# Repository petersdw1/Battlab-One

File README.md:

# BattLab-One
A New Tool for Estimating and Optimizing Battery Life for Your Next Internet of Things Project

  - Battlab-One Quick Start Guide

  - BattLab_One_Production_Rev_A.py - Python Application Code for Production version 1.01

  - Production_Rev_A.sch - Schematic in Eagle

  - Production_Rev_A..brd - PCB Layout in Eagle

  - MSP430Firmware.c - Firmware code for the MSP430 for Production Version 1.01

  - BOM_Production_Rev_A - Bill of Materials for Battlab-One Production Rev A

  - 98-bluebird-labs.rules - Linux udev rules for Battlab-One

  See more at www.bluebird-labs.com

# Development

This project uses pipenv to take care of setting up a virtual environment as well as managing the dependencies needed.

1. Install pipenv as describe here https://pypi.org/project/pipenv/
2. Start a terminal and change to the root folder of this project.
3. Run pipenv to setup the environment: `pipenv install --dev`
4. Start the pipenv shell: `pipenv shell`
5. Start the application: `python BattLab_One_V1.0.6.py`

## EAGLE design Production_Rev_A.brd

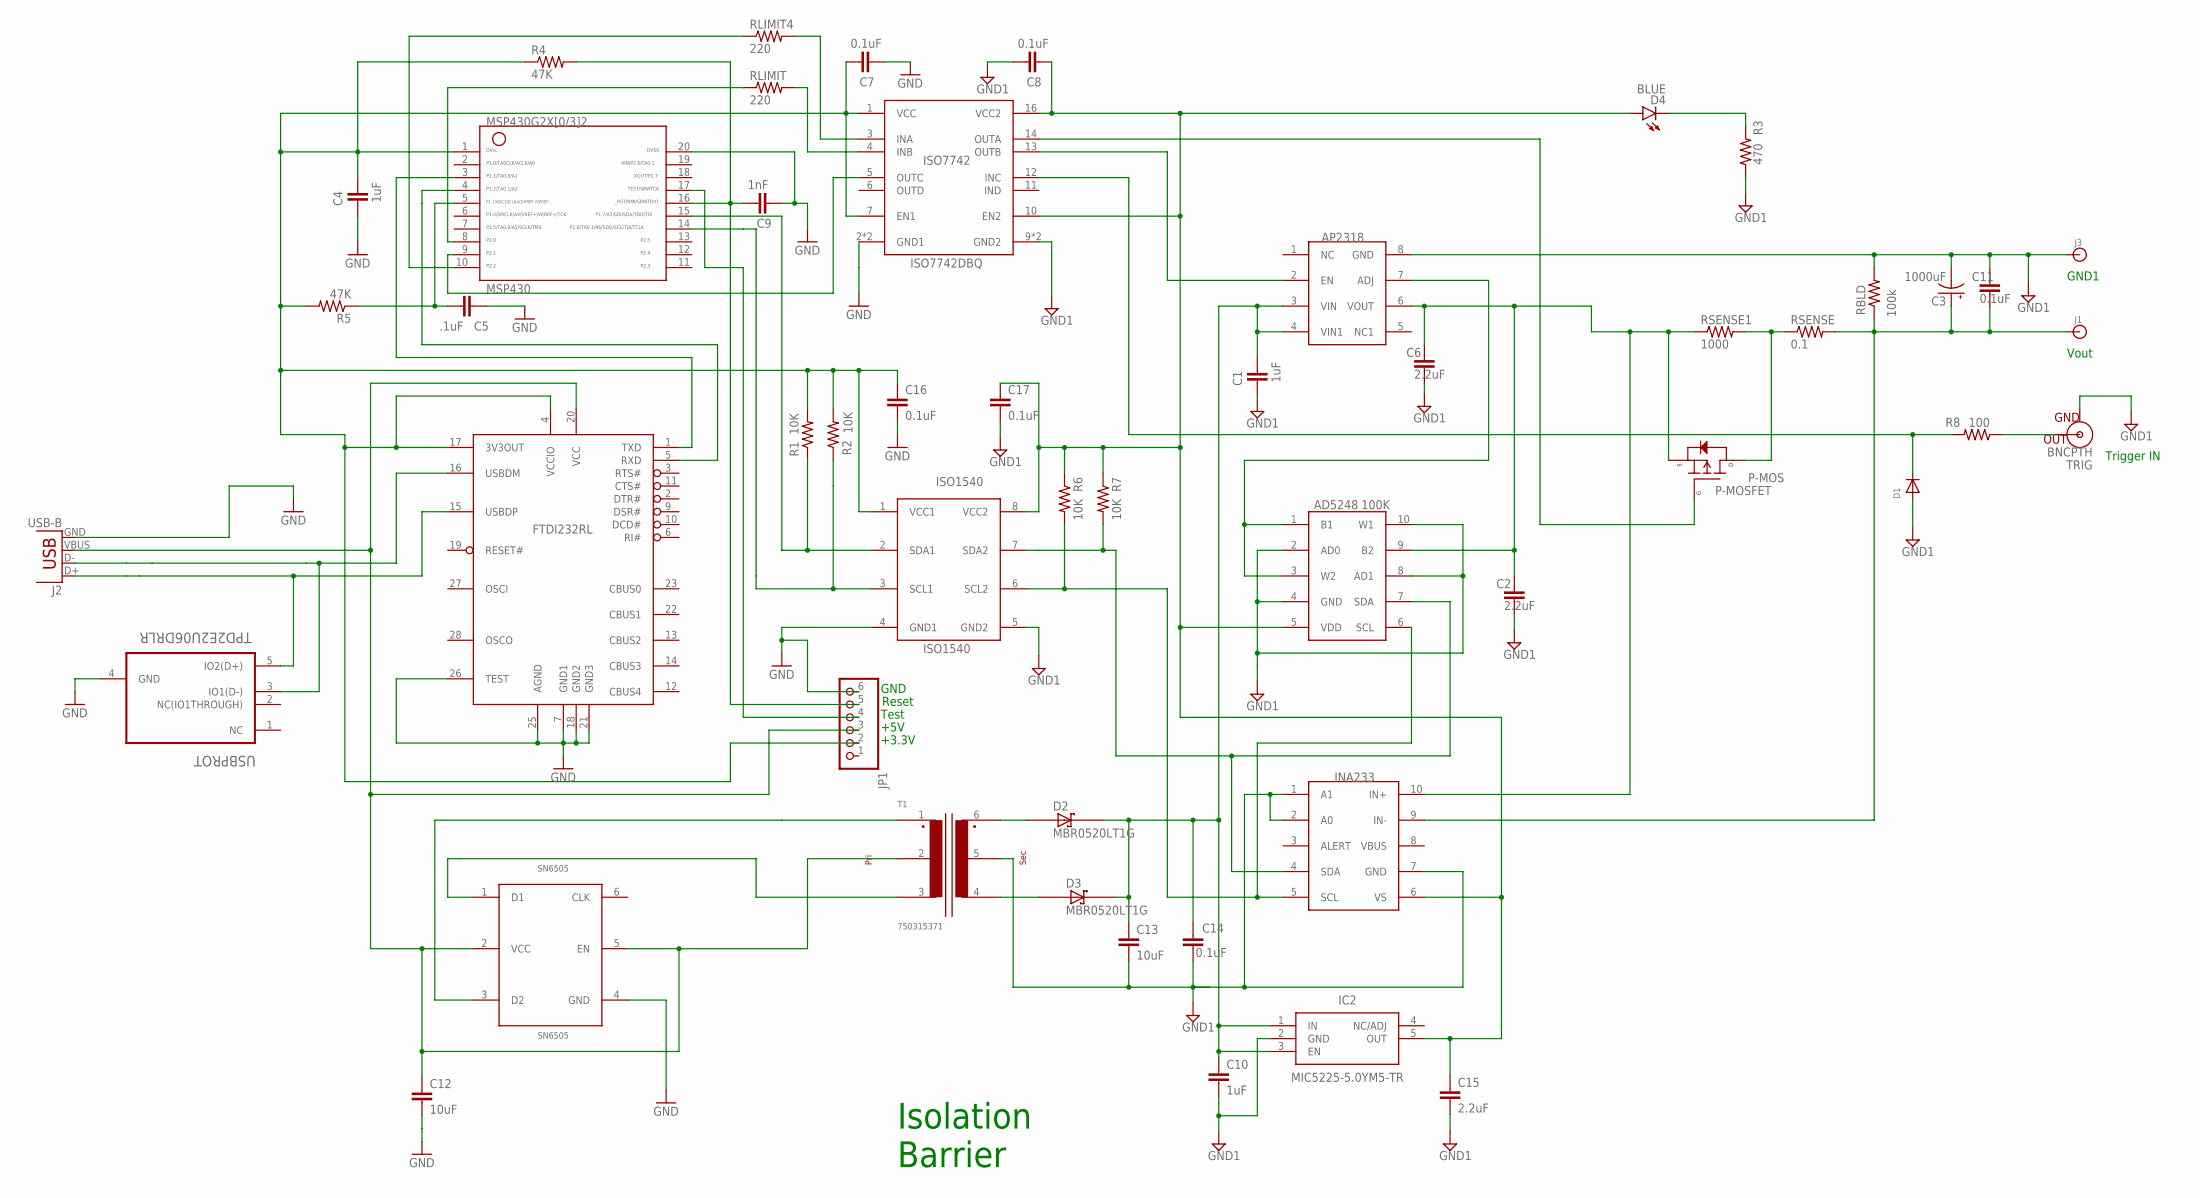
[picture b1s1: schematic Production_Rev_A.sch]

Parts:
AD5248: 100K; MSOP-10
AP2318: AP2318; SOIC-8
C1, C4, C10: 1uF; 1206
C2, C6, C15: 2.2uF; 1206
C3: 1000uF; PANASONIC_F
C5: .1uF; 1206
C7, C8, C11, C14, C16, C17: 0.1uF; 1206
C9: 1nF; 1206
C12, C13: 10uF; 1206
D1: DIODESOD-123; SOD-123
D2, D3: MBR0520LT1G; SOD3716X117(SOD-123)
D4: BLUE; LED-1206
FTDI232RL: FT232RL; SSOP28DB
IC2: MIC5225-5.0YM5-TR; SOT95P280X130-5N
INA233: INA233; VSSOP-10
ISO1540: ISO1540; SOIC127P600X175-8N
ISO7742: ISO7742DBQ; SOP63P599X175-16N
J1, J3: BANANA_CONN
J2: USB-B; USB-B-PTH
JP1: PINHD-1X6; 1X06
MSP430: MSP430; PW20
P-MOS: P-MOSFET; SOT23-3
R1, R2, R6, R7: 10K; 1206
R3: 470; 1206
R4, R5: 47K; 1206
R8: 100; 1206
RBLD: 100k; 1206
RLIMIT, RLIMIT4: 220; 1206
RSENSE: 0.1; 1206
RSENSE1: 1000; 1206
SN6505: SN6505; SOT95P280X145-6N
T1: 750315371; TOR-6P-HT4_SMT_6PIN_(1201)
TRIG: BNCPTH; BNC
USBPROT: TPD2E2U06DRLR; SOT50P160X60-5N

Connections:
3.3V: C4.2, C7.2, C16.1, FTDI232RL.4 (VCCIO), FTDI232RL.17 (3V3OUT), ISO1540.1 (VCC1), ISO7742.1 (VCC), ISO7742.7 (EN1), JP1.2, MSP430.1, R1.2, R2.2, R4.1, R5.2
+5V_LDO: AD5248.5 (VDD), C8.1, C15.1, C17.1, D4.A, IC2.5 (OUT), INA233.6 (VS), ISO1540.8 (VCC2), ISO7742.10 (EN2), ISO7742.16 (VCC2), R6.1, R7.1
GND: C4.1, C5.1, C7.1, C9.1, C12.2, C16.2, FTDI232RL.7 (GND1), FTDI232RL.18 (GND2), FTDI232RL.21 (GND3), FTDI232RL.25 (AGND), FTDI232RL.26 (TEST), ISO1540.4 (GND1), ISO7742.2 (GND1), ISO7742.8 (GND1), J2.GND, JP1.6, MSP430.20, SN6505.4 (GND), USBPROT.4 (GND)
GND1: AD5248.2 (AD0), AD5248.4 (GND), AD5248.8 (AD1), AD5248.10 (W1), AP2318.8 (GND), C1.1, C2.2, C3.-, C6.2, C8.2, C10.2, C11.1, C13.2, C14.2, C15.2, C17.2, D1.A, IC2.2 (GND), INA233.1 (A1), INA233.2 (A0), INA233.7 (GND), ISO1540.5 (GND2), ISO7742.9 (GND2), ISO7742.15 (GND2), J3.P$1, R3.1, RBLD.2, T1.5, TRIG.GND
LDO_EN: ISO7742.4 (INB), RLIMIT.2
LDO_EN1: MSP430.8, RLIMIT.1
LDO_EN2: AP2318.2 (EN), ISO7742.13 (OUTB)
unnamed: P-MOS.3 (D), RSENSE.1, RSENSE1.2
unnamed: AP2318.3 (VIN), AP2318.4 (VIN1), C1.2, C10.1, C13.1, C14.1, D2.1 (C), D3.1 (C), IC2.1 (IN), IC2.3 (EN)
unnamed: D3.2 (A), T1.4
unnamed: D2.2 (A), T1.6
unnamed: AD5248.1 (B1), AD5248.3 (W2), AP2318.7 (ADJ)
unnamed: D4.C, R3.2
unnamed: R8.1, TRIG.S (OUT)
NC: USBPROT.1 (NC)
RESET: C9.2, JP1.5, MSP430.16, R4.2
RS_EN: MSP430.10, RLIMIT4.1
RS_EN1: ISO7742.3 (INA), RLIMIT4.2
RS_EN2: ISO7742.14 (OUTA), P-MOS.1 (G)
SCL1: ISO1540.3 (SCL1), MSP430.14, R2.1
SCL2: AD5248.6 (SCL), INA233.5 (SCL), ISO1540.6 (SCL2), R6.2
SDA1: ISO1540.2 (SDA1), MSP430.15, R1.1
SDA2: AD5248.7 (SDA), INA233.4 (SDA), ISO1540.7 (SDA2), R7.2
TEST: JP1.4, MSP430.17
TRANS1: SN6505.3 (D2), T1.1
TRANS3: SN6505.1 (D1), T1.3
TRIGGER_MSP1: ISO7742.5 (OUTC), MSP430.9
TRIGGER_MSP2: D1.C, ISO7742.12 (INC), R8.2
UART_RX: FTDI232RL.5 (RXD), MSP430.4
UART_TX: FTDI232RL.1 (TXD), MSP430.3
USB+: FTDI232RL.15 (USBDP), J2.D+, USBPROT.5 (IO2(D+))
USB-: FTDI232RL.16 (USBDM), J2.D-, USBPROT.3 (IO1(D-))
VBUS+5V: C12.1, FTDI232RL.20 (VCC), J2.VBUS, JP1.3, SN6505.2 (VCC), SN6505.5 (EN), T1.2
VOUT: C3.+, C11.2, INA233.9 (IN-), J1.P$1, RBLD.1, RSENSE.2
VREF: C5.2, MSP430.5, R5.1
V_OUT: AD5248.9 (B2), AP2318.6 (VOUT), C2.1, C6.1, INA233.10 (IN+), P-MOS.2 (S), RSENSE1.1

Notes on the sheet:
Isolation Barrier
Test
Reset
GND
+5V
GND1
Vout
Trigger IN
+3.3V

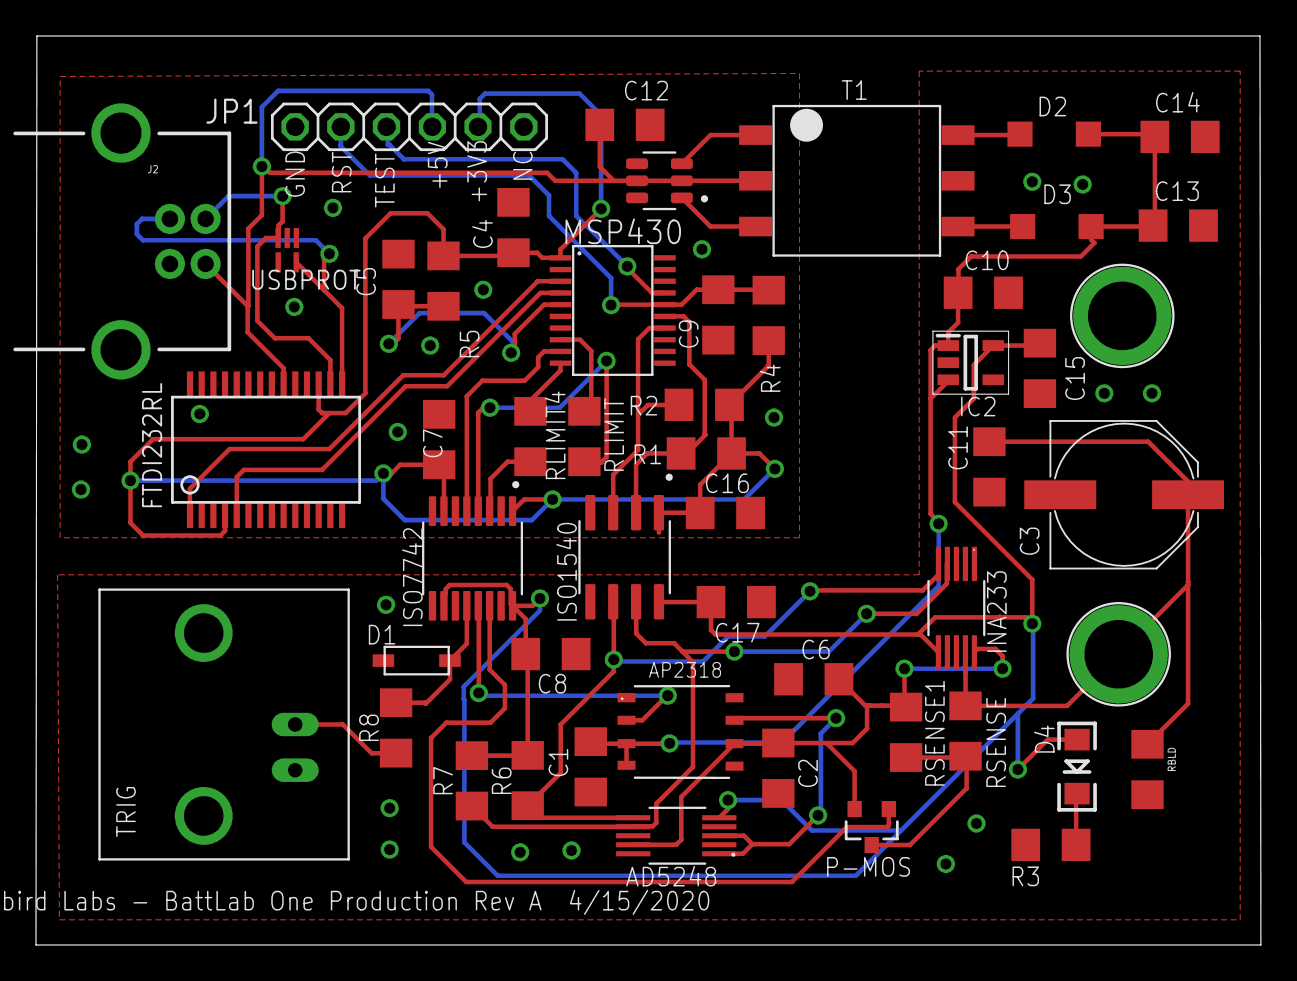
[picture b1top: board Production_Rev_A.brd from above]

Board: 2 copper layers, 68.0 x 50.5 mm, 51 parts (0 on the bottom side), 35 nets.

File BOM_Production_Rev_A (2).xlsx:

Part | Value | Device | Package | Description
AD5248 | 100K | AD5248 | MSOP-10 | Digital potentiometer
AP2318 |  | AP2318 | SOIC-8 | Voltage Regulator
C1 | 1uF | CAP1206 | 1206 | Capacitor
C2 | 2.2uF | CAP1206 | 1206 | Capacitor
C3 | 1000uF | CPOL-USF | PANASONIC_F | POLARIZED CAPACITOR
C4 | 1uF | CAP1206 | 1206 | Capacitor
C5 | .1uF | CAP1206 | 1206 | Capacitor
C6 | 2.2uF | CAP1206 | 1206 | Capacitor
C7 | 0.1uF | CAP1206 | 1206 | Capacitor
C8 | 0.1uF | CAP1206 | 1206 | Capacitor
C9 | 1nF | CAP1206 | 1206 | Capacitor
C10 | 1uF | CAP1206 | 1206 | Capacitor
C11 | 0.1uF | CAP1206 | 1206 | Capacitor
C12 | 10uF | CAP1206 | 1206 | Capacitor
C13 | 10uF | CAP1206 | 1206 | Capacitor
C14 | 0.1uF | CAP1206 | 1206 | Capacitor
C15 | 2.2uF | CAP1206 | 1206 | Capacitor
C16 | 0.1uF | CAP1206 | 1206 | Capacitor
C17 | 0.1uF | CAP1206 | 1206 | Capacitor
D1 |  | DIODESOD-123 | SOD-123 | Diode
D2 | MBR0520LT1G | MBR0520LT1G | SOD3716X117(SOD-123) | Surface Mount Schottky Power Rectifier Plastic SODâˆ’123 Package
D3 | MBR0520LT1G | MBR0520LT1G | SOD3716X117(SOD-123) | Surface Mount Schottky Power Rectifier Plastic SODâˆ’123 Package
D4 | BLUE | LED-BLUE1206 | LED-1206 | Blue LEDs for production use
FTDI232RL |  | FT232RL | SSOP28DB | USB UART
IC2 | MIC5225-5.0YM5-TR | MIC5225-5.0YM5-TR | SOT95P280X130-5N | MICROCHIP - MIC5225-5.0YM5-TR - LDO VOLT REG
INA233 |  | INA233 | VSSOP-10 | Texas Instruments current measurement
ISO1540 | ISO1540 | ISO1540 | SOIC127P600X175-8N | i2c Isolation
ISO7742 | ISO7742DBQ | ISO7742DBQ | SOP63P599X175-16N | High-Efficiency
J1 |  | BANANA_CONN | BANANA_CONN | Through-hole banana jack
J2 | USB-B | USBPTH | USB-B-PTH | USB Connectors
J3 |  | BANANA_CONN | BANANA_CONN | Through-hole banana jack
JP1 |  | PINHD-1X6 | 1X06 | PIN HEADER
MSP430 | MSP430 | G2X[0/3]2---PW20 | PW20 | MSP430G2X[0/3]2
P-MOS | P-MOSFET | P-CHANNEL-MOSFET | SOT23-3 | P-Channel MOSFET Mode Field Effect Transistor
R1 | 10K | RESISTOR1206 | 1206 | Resistor
R2 | 10K | RESISTOR1206 | 1206 | Resistor
R3 | 470 | RESISTOR1206 | 1206 | Resistor
R4 | 47K | RESISTOR1206 | 1206 | Resistor
R5 | 47K | RESISTOR1206 | 1206 | Resistor
R6 | 10K | RESISTOR1206 | 1206 | Resistor
R7 | 10K | RESISTOR1206 | 1206 | Resistor
R8 | 100 | RESISTOR1206 | 1206 | Resistor
RBLD | 100k | RESISTOR1206 | 1206 | Resistor
RLIMIT | 220 | RESISTOR1206 | 1206 | Resistor
RLIMIT4 | 220 | RESISTOR1206 | 1206 | Resistor
RSENSE | 0.1 | RESISTOR1206 | 1206 | Resistor
RSENSE1 | 100 | RESISTOR1206 | 1206 | Resistor
SN6505 | SN6505 | SN6505 | SOT95P280X145-6N | DC-DC Driver
T1 | 750315371 | 750315371 | TOR-6P-HT4_SMT_6PIN_(1201) | Transformer 1.1:1
TRIG | BNCPTH | BNCPTH | BNC | BNC Connector
USBPROT | TPD2E2U06DRLR | TPD2E2U06DRLR | SOT50P160X60-5N | LOW-CAPACITANCE 2-CHANNEL Â±25kv contact and +/-30kv air gap protection for USB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

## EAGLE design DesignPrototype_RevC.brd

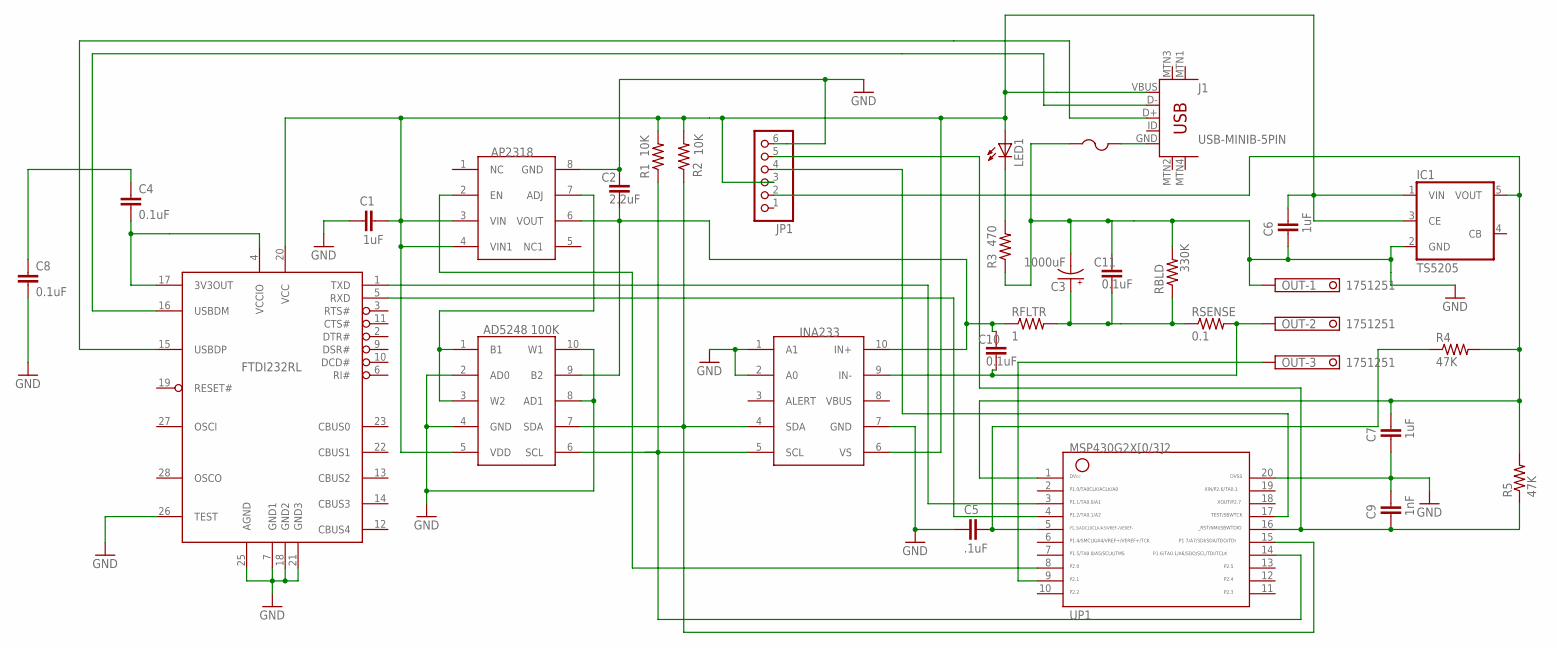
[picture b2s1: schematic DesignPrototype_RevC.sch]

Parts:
AD5248: 100K; MSOP-10
AP2318: AP2318; SOIC-8
C1, C6, C7: 1uF; 1206
C2: 2.2uF; 1206
C3: 1000uF; PANASONIC_F
C4, C8, C10, C11: 0.1uF; 1206
C5: .1uF; 1206
C9: 1nF; 1206
FTDI232RL: FT232RL; SSOP28DB
FUSE1: PTCFUSE-1206; R1206
IC1: TS5205; SOT25
INA233: INA233; VSSOP-10
J1: USB-MINIB-5PIN; USB-MINIB
JP1: PINHD-1X6; 1X06
LED1: LEDCHIPLED_1206; CHIPLED_1206
OUT: 1751251
R1, R2: 10K; 1206
R3: 470; 1206
R4, R5: 47K; 1206
RBLD: 330K; 1206
RFLTR: 1; 1206
RSENSE: 0.1; 1206
UP1: MSP430; PW20

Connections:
GND: AD5248.2 (AD0), AD5248.4 (GND), AD5248.8 (AD1), AD5248.10 (W1), AP2318.8 (GND), C1.1, C2.1, C3.-, C5.1, C6.1, C7.1, C8.2, C9.2, C11.1, FTDI232RL.7 (GND1), FTDI232RL.18 (GND2), FTDI232RL.21 (GND3), FTDI232RL.25 (AGND), FTDI232RL.26 (TEST), FUSE1.1, IC1.2 (GND), INA233.1 (A1), INA233.2 (A0), INA233.7 (GND), JP1.6, OUT.1, R3.1, RBLD.2, UP1.20
unnamed: AD5248.7 (SDA), INA233.4 (SDA), R2.1, UP1.15
unnamed: FTDI232RL.5 (RXD), UP1.4
unnamed: FTDI232RL.1 (TXD), UP1.3
unnamed: AD5248.6 (SCL), INA233.5 (SCL), R1.1, UP1.14
unnamed: FTDI232RL.16 (USBDM), J1.D-
unnamed: FTDI232RL.15 (USBDP), J1.D+
unnamed: AP2318.2 (EN), UP1.8
unnamed: FUSE1.2, J1.GND
unnamed: C3.+, C11.2, RBLD.1, RFLTR.2, RSENSE.1
unnamed: AD5248.1 (B1), AD5248.3 (W2), AP2318.7 (ADJ)
unnamed: C10.2, INA233.9 (IN-), OUT.2, RSENSE.2
unnamed: C4.2, FTDI232RL.4 (VCCIO), FTDI232RL.17 (3V3OUT)
unnamed: JP1.4, UP1.17
unnamed: LED1.C, R3.2
unnamed: C5.2, R4.1, UP1.5
unnamed: AD5248.9 (B2), AP2318.6 (VOUT), C2.2, C10.1, INA233.10 (IN+), RFLTR.1
unnamed: C7.2, IC1.5 (VOUT), JP1.2, R4.2, R5.2, UP1.1
unnamed: C9.1, JP1.5, R5.1, UP1.16
unnamed: OUT.3, UP1.9
unnamed: C4.1, C8.1
unnamed: AD5248.5 (VDD), AP2318.3 (VIN), AP2318.4 (VIN1), C1.2, C6.2, FTDI232RL.20 (VCC), IC1.1 (VIN), IC1.3 (CE), INA233.6 (VS), J1.VBUS, JP1.3, LED1.A, R1.2, R2.2

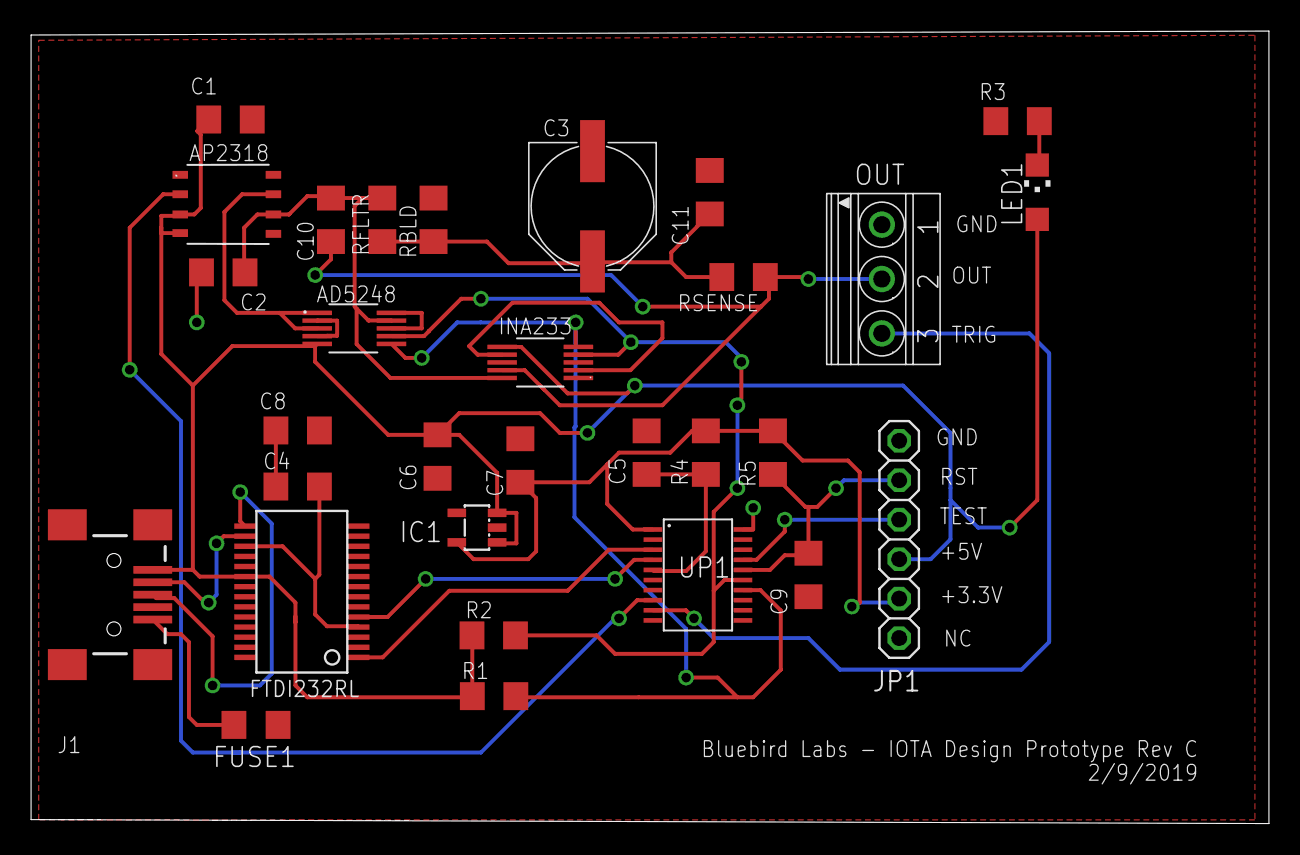
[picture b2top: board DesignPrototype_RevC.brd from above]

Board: 2 copper layers, 79.7 x 51.0 mm, 30 parts (0 on the bottom side), 22 nets.

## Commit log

2020-08-23 Add missing icons from the zip file as well as first step to make it more compatible with Linux.
2020-08-23 Introduce pipenv for making it easier to develop cross-platform and to manage dependencies.
2020-09-13 Adding Linux udev rules for BattLab One
2020-09-21 Fix for exiting the application.
    The root window was destroyed, but the mainloop was still running. By using quit() the mainloop will terminate and the program will exit.
2020-09-22 Fix for exiting the application. (#7)
    * Fix for exiting the application.
    The root window was destroyed, but the mainloop was still running. By using quit() the mainloop will terminate and the program will exit.
    * Update BattLab_One_V1.0.6.py
2020-09-22 Rename BattLab_One_V1.0.6.py to BattLab_One_V1.0.6.1.py
2020-09-22 Rename BattLab_One_V1.0.6.1.py to BattLab_One_V1.0.6.py
2020-09-22 Update BattLab_One_V1.0.6.py (#8)
2020-09-23 Rename BattLab_One_V1.0.6.py to BattLab_One_V1.0.7.py
2020-09-23 Rename BattLab_One_V1.0.7.py to BattLab_One_V1.0.8.py
2020-09-26 Added V1.09
2020-09-28 Introduce pipenv for making it easier to develop cross-platform and to manage dependencies. (#2)
2020-09-28 Adding Linux udev rules for BattLab One (#5)
2020-10-05 Rename BattLab_One_V1.0.9.py to BattLab_One_V1_0_9.py
2020-10-09 Minor fix re serial numbers
    Just a minor fix for crashes on short FTDI device serial numbers. I have an old custom adapter with a single digit serial number.
2020-10-09 More reliable way to get device name
    The grep doesn't always select the correct entry in list_ports if there are multiple with the same VID:PID. Only verified to work on Windows, but I'd expect pyserial device name handling to be pretty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
2020-10-09 Revert "More reliable way to get device name"
    This reverts commit 2437c60cc06743da3da4ab4c7f73bea7f066cfd6.
2020-10-09 Revert "Minor fix re serial numbers"
    This reverts commit d6ad231f2ca751d9f97363872ab277c8c541bb2c.
2020-10-09 Revert "Revert "More reliable way to get device name""
    This reverts commit abd7d18d120d5fe82339900bee30acf4975eb6ab.
2020-10-09 Minor fix re FTDI serial numbers
    Just a minor fix for crashes on short FTDI device serial numbers. I have an old custom adapter with a single digit serial number.
2020-10-09 More reliable way to get device name
    The grep doesn't always select the correct entry in list_ports if there are multiple with the same VID:PID.
    Only verified to work on Windows, but I'd expect pyserial device name handling to be pretty cross platform.
2020-12-03 Rename BattLab_One_V1.1.0.py to BattLab_One_V1.1.1.py
2020-12-12 Add 3D printable enclosure
2020-12-12 Add 3D printable enclosure (#17)
2021-03-19 Bump pillow from 7.2.0 to 8.1.1
    Bumps [pillow](https://github.com/python-pillow/Pillow) from 7.2.0 to 8.1.1.
    - [Release notes](https://github.com/python-pillow/Pillow/releases)
    - [Changelog](https://github.com/python-pillow/Pillow/blob/master/CHANGES.rst)
    - [Commits](https://github.com/python-pillow/Pillow/compare/7.2.0...8.1.1)
2021-06-08 Bump pillow from 7.2.0 to 8.2.0
    Bumps [pillow](https://github.com/python-pillow/Pillow) from 7.2.0 to 8.2.0.
    - [Release notes](https://github.com/python-pillow/Pillow/releases)
    - [Changelog](https://github.com/python-pillow/Pillow/blob/master/CHANGES.rst)
    - [Commits](https://github.com/python-pillow/Pillow/compare/7.2.0...8.2.0)
    ---
    updated-dependencies:
2021-06-29 Rename MSP430.Firmware_Production_Rev_1.03.c.c to MSP430.Firmware_Production_Rev_1.03.c
2021-09-08 Bump pillow from 7.2.0 to 8.3.2
    Bumps [pillow](https://github.com/python-pillow/Pillow) from 7.2.0 to 8.3.2.
    - [Release notes](https://github.com/python-pillow/Pillow/releases)
    - [Changelog](https://github.com/python-pillow/Pillow/blob/master/CHANGES.rst)
    - [Commits](https://github.com/python-pillow/Pillow/compare/7.2.0...8.3.2)
    ---
    updated-dependencies:
2022-01-13 Bump pillow from 7.2.0 to 9.0.0
    Bumps [pillow](https://github.com/python-pillow/Pillow) from 7.2.0 to 9.0.0.
    - [Release notes](https://github.com/python-pillow/Pillow/releases)
    - [Changelog](https://github.com/python-pillow/Pillow/blob/main/CHANGES.rst)
    - [Commits](https://github.com/python-pillow/Pillow/compare/7.2.0...9.0.0)
    ---
    updated-dependencies:
2022-03-12 Bump pillow from 7.2.0 to 9.0.1
    Bumps [pillow](https://github.com/python-pillow/Pillow) from 7.2.0 to 9.0.1.
    - [Release notes](https://github.com/python-pillow/Pillow/releases)
    - [Changelog](https://github.com/python-pillow/Pillow/blob/main/CHANGES.rst)
    - [Commits](https://github.com/python-pillow/Pillow/compare/7.2.0...9.0.1)
    ---
    updated-dependencies:
2022-11-22 Bump pillow from 7.2.0 to 9.3.0
    Bumps [pillow](https://github.com/python-pillow/Pillow) from 7.2.0 to 9.3.0.
    - [Release notes](https://github.com/python-pillow/Pillow/releases)
    - [Changelog](https://github.com/python-pillow/Pillow/blob/main/CHANGES.rst)
    - [Commits](https://github.com/python-pillow/Pillow/compare/7.2.0...9.3.0)
    ---
    updated-dependencies:
2022-12-08 Bump certifi from 2020.6.20 to 2022.12.7
    Bumps [certifi](https://github.com/certifi/python-certifi) from 2020.6.20 to 2022.12.7.
    - [Release notes](https://github.com/certifi/python-certifi/releases)
    - [Commits](https://github.com/certifi/python-certifi/compare/2020.06.20...2022.12.07)
    ---
    updated-dependencies:
    - dependency-name: certifi

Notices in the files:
parts and their libraries:
SparkFun-Capacitors: Licensing: Creative Commons ShareAlike 4.0 International - https://creativecommons.org/licenses/by-sa/4.0
